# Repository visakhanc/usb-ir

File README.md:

USB-IR - IR receiver based on V-USB
===================================

USB-IR is an infrared remote control receiver with a USB communication enabled by v-usb usb stack. So, it can be programmed as an IR receiver for PC with specific functions assigned to various keys of a remote control.

HID Bootloader option
---------------------

Firmware updates can be done through USB itself! For this, HID bootloader should be initially flashed into the AVR through ISP pins. After this, to program firmware using bootloader, just plug in the USB while pressing and holding the button. It will get detected as 'HIDBoot' device. Now use the command line tool for HID bootloader to program hex files. like this:
bootloadHID.exe -r main.hex

Find the HID bootloader here: [HID bootloader](https://github.com/visakhanc/vusb_projects/tree/master/bootloadHID.2012-12-08)

Examples
--------

[HID IR Remote](https://github.com/visakhanc/usb-ir/blob/master/firmware/hid-ir-remote) : Demonstrates the usage of USB-IR as a multimedia remote control receiver for PC. Sony IR protocol (SIRC) is used here. Implemented functions are: Volume Up/Down, Next, Previous, Pause, Play, Stop, Mute.

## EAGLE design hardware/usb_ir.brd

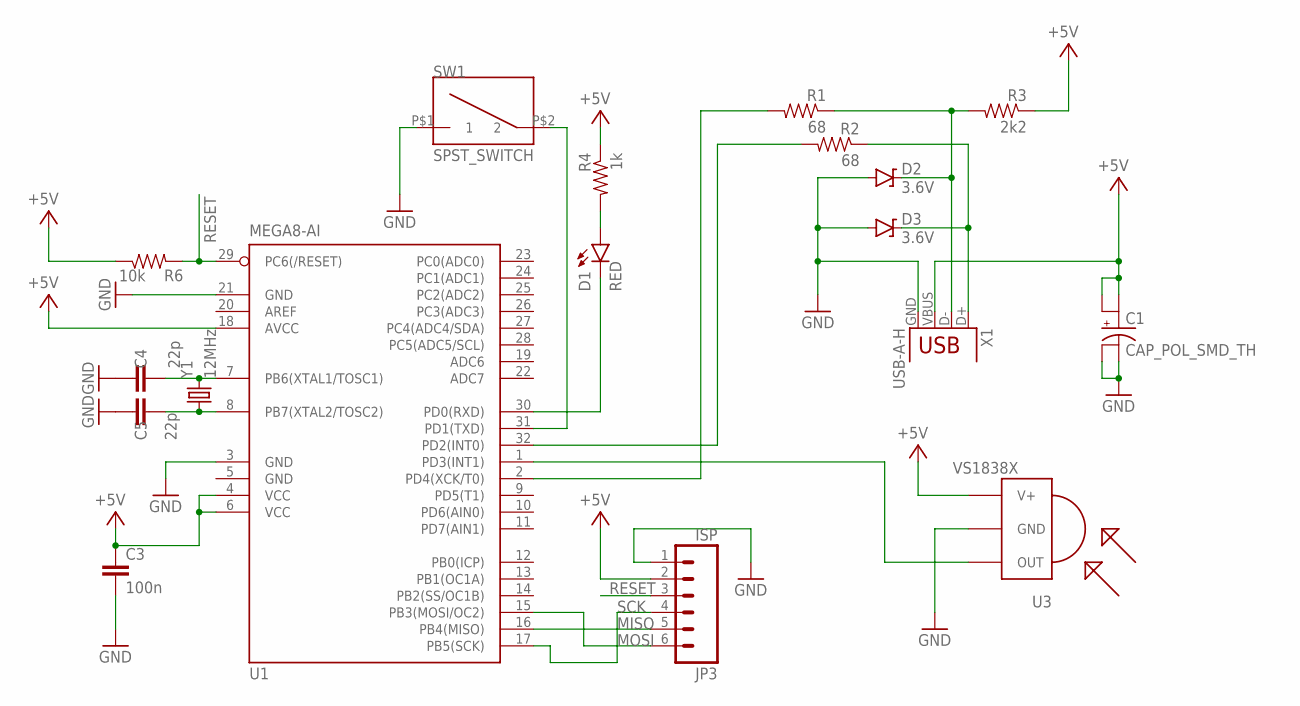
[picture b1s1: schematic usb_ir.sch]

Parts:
C1: CAP_POL_SMD_TH; CAP_SMD_TH_5X5
C3: 100n; 1206
C4, C5: 22p; 1206
D1: RED; LED-1206
D2, D3: 3.6V; DIODE-ZENER
JP3: ISP; 1X06-SMD_EDGE
R1, R2: 68; 1206
R3: 2k2; 1206
R4: 1k; 1206
R6: 10k; 1206
SW1: SPST_SWITCH; SMD_TACT_SWITCH
U1: MEGA8-AI; TQFP32-08
U3: VS1838X
X1: USB-A-H
Y1: 12MHz; HC49UP

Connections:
+5V: C1.+, C1.+TH (+), C3.1, JP3.2, R3.1, R4.1, R6.1, U1.4 (VCC), U1.6 (VCC), U1.18 (AVCC), U3.VCC (V+), X1.VBUS
GND: C1.-, C1.-TH (-), C3.2, C4.1, C5.1, D2.P$2 (A), D3.P$2 (A), JP3.1, SW1.P$1 (1), U1.3 (GND), U1.5 (GND), U1.21 (GND), U3.GND, X1.GND
MISO: JP3.5, U1.16 (PB4(MISO))
MOSI: JP3.6, U1.15 (PB3(MOSI/OC2))
unnamed: U1.1 (PD3(INT1)), U3.OUT
unnamed: D2.P$1 (C), R1.1, R3.2, X1.D-
unnamed: D3.P$1 (C), R2.1, X1.D+
unnamed: R2.2, U1.32 (PD2(INT0))
unnamed: R1.2, U1.2 (PD4(XCK/T0))
unnamed: D1.C, U1.30 (PD0(RXD))
unnamed: SW1.P$2 (2), U1.31 (PD1(TXD))
unnamed: D1.A, R4.2
unnamed: C4.2, U1.7 (PB6(XTAL1/TOSC1)), Y1.2
unnamed: C5.2, U1.8 (PB7(XTAL2/TOSC2)), Y1.1
RESET: JP3.3, R6.2, U1.29 (PC6(/RESET))
SCK: JP3.4, U1.17 (PB5(SCK))

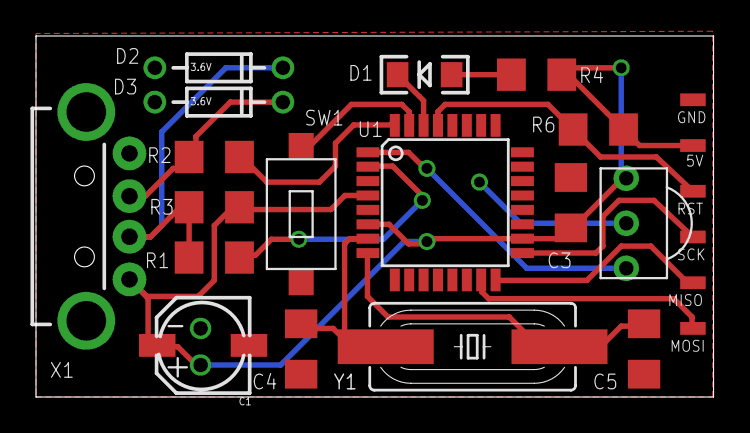
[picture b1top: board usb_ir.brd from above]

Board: 2 copper layers, 37.6 x 20.1 mm, 18 parts (0 on the bottom side), 16 nets.

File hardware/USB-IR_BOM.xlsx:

Qty | Value | Device | Package | Parts | Description | Price
1 | 100n | CAP1206 | 1206 | C3 | Capacitor | 0.5
1 | 10k | RESISTOR1206 | 1206 | R6 | Resistor | 0.5
1 | 12MHz | CRYSTALSMD | HC49UP | Y1 | Various standard crystals. Proven footprints. | 12
1 | 1k | RESISTOR1206 | 1206 | R4 | Resistor | 0.5
2 | 22p | CAP1206 | 1206 | C4, C5 | Capacitor | 0.5
1 | 2k2 | RESISTOR1206 | 1206 | R3 | Resistor | 0.5
2 | 3.6V | DIODE-ZENERPTH | DIODE-ZENER | D2, D3 | Zener Diode | 2
2 | 68 | RESISTOR1206 | 1206 | R1, R2 | Resistor | 0.5
1 | CAP_POL_SMD_TH | CAP_POL_SMD_TH | CAP_SMD_TH_5X5 | C1 |  | 8
1 | MEGA8-AI | MEGA8-AI | TQFP32-08 | U1 | MICROCONTROLLER | 80
1 | RED | LED1206 | LED-1206 | D1 | LED | 2
1 | SPST_SWITCH | SPST_SWITCH | SMD_TACT_SWITCH | SW1 |  | 4
1 | USB-A-H | USB-A-H | USB-A-H | X1 | USB Connectors | 12
1 | VS1838X | VS1838X | VS1838X | U3 | VS1838 IR demodulator with supply rangeof 2.7V to 5V | 20
 |  |  |  |  | TOTAL | 146

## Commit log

2017-03-16 Added Readme
2017-03-16 Readme modified
2017-03-17 Modified Readme
2017-03-17 Modified pics

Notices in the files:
parts and their libraries:
SparkFun-Connectors: Licensing: Creative Commons ShareAlike 4.0 International - https://creativecommons.org/licenses/by-sa/4.0
